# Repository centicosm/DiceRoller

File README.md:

# Yet Another Dice Roller
Dual 7-segment LED PIC uC dice rolling toy with schematic. pcb, and 3d-printable case

Selectable dice types: 1d2, 2d2, 1d4, 2d4, 1d6, 2d6, 1d8, 2d8, 1d10, 1d12, 1d100, 1d20.<br>
Display will auto-shutoff after around 10s

MPLab X with XC8 toolchain used.

For the uC used (a PIC 16F88) after programming the chip the first time, Vpp first programming mode must be used to reflash firmware as the internal oscillator is used along with all available pins (MCLR).

BOM
----------------------------------------------------------------
PIC 16F88 PDIP<br>
10K 1/4 Watt Resistor<br>
10 1/4 Watt Resistor<br>
.33uF Capacitor<br>
.1uF Capacitor<br>
2 NTE3078 7-Segment LED<br>
LM340T5 (TO-220)<br>
9V Battery connector<br>
6.2mm cutout pushbutton switch (e.g. GPB024A05BB)<br>
12mm cutout pushbutton switch<br>
15mm Panel mount SPDT On-Off Switch (e.g. EG1201)

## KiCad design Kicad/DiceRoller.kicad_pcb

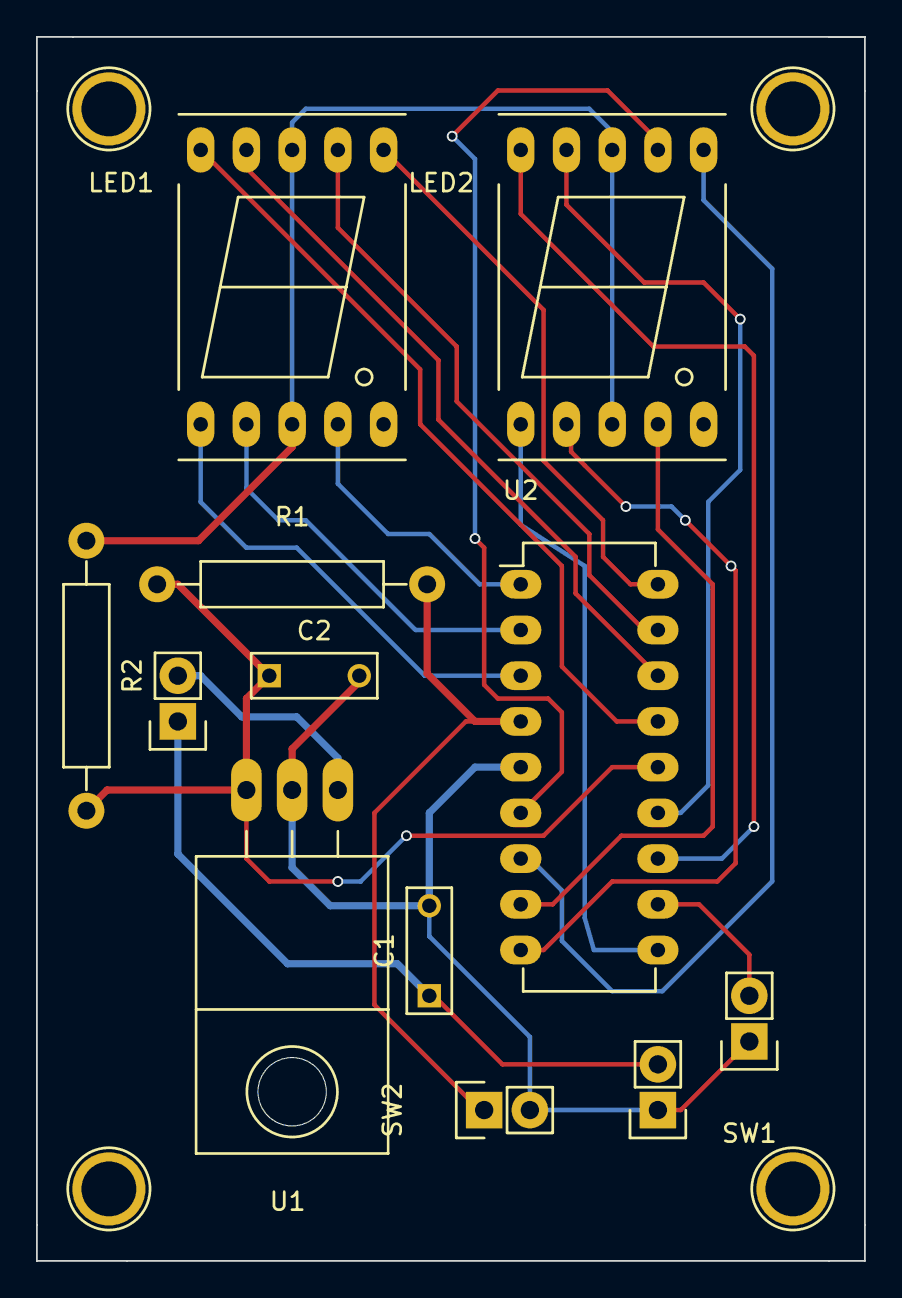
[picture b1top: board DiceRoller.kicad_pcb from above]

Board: 2 copper layers, 46.0 x 68.0 mm, 10 parts (0 on the bottom side), 19 nets.

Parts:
C1: .33uF; C_Rect_L7_W2.5_P5
C2: .1; C_Rect_L7_W2.5_P5
LED1, LED2: NTE3078; 7SegmentLED_LTS6760_LTS6780
R1: 10k; Resistor_Horizontal_RM15mm
R2: 10; Resistor_Horizontal_RM15mm
SW1, SW2: SW_PUSH; Pin_Header_Straight_1x02
U1: 7805; TO-220_Neutral123_Horizontal_LargePads
U2: PIC16(L)F88-I/P; DIP-18_W7.62mm_LongPads

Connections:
unnamed: C1.2, C2.2, SW1.1, SW2.2, U1.2, U2.5
unnamed: C2.1, R1.1, R2.2, U1.3, U2.14
unnamed: LED1.1, U2.3
unnamed: LED1.2, U2.2
unnamed: LED1.3, LED1.8, LED2.3, LED2.8, R2.1
unnamed: LED1.4, U2.1
unnamed: LED1.6, U2.18
unnamed: LED1.7, U2.17
unnamed: LED1.9, U2.16
unnamed: LED1.10, U2.15
unnamed: LED2.1, U2.10
unnamed: LED2.2, U2.9
unnamed: LED2.4, U2.8
unnamed: LED2.6, U2.7
unnamed: LED2.7, U2.6
unnamed: LED2.9, U2.13
unnamed: LED2.10, U2.12
unnamed: R1.2, SW2.1, U2.4
unnamed: SW1.2, U2.11

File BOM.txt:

PIC 16F88 PDIP
10K 1/4 Watt Resistor
10 1/4 Watt Resistor
.33uF Capacitor
.1uF Capacitor
2 NTE3078 7-Segment LED
LM340T5 (TO-220)
9V Battery connector
6.2mm cutout pushbutton switch (e.g. GPB024A05BB)
12mm cutout pushbutton switch
15mm Panel mount SPDT On-Off Switch (e.g. EG1201)

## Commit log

2015-12-16 :confetti_ball: Added .gitattributes & .gitignore files
2015-12-16 PIC uController Electronic Dice
    Dual 7-segment LED PIC microcontroller-based dice rolling toy with KiCad
    schematic, pcb, and 3d-printable case
2015-12-16 Added images for readme
2016-01-16 Swapped Buttons on MCU for adding sleep/wake capability
